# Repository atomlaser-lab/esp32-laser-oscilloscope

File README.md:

# ESP32 Remote Oscilloscope + MOGLabs DLC control

This project is a remote browser-based oscilloscope and controller intended for monitoring, toggling and adjusting the frequency lock on a MOGLabs Diode Laser Controller (DLC). An ESP32 development board interfaces with the DLC and hosts a dashboard webpage.

This README contains [Instructions](#instructions) for setting up and using the project as well as useful [Background information](#background). A list of [bugs and suggested improvements](#bugs-and-improvements) is at the end. The project was developed and tested using the PlatformIO Extension in VSCode, with a model 502 DLC. It requires an ESP32-DevkitC development board (see [specs, board comparison & resources](https://www.espressif.com/en/products/devkits/esp32-devkitc)), and should work with either WROVER or WROOM versions. It was tested with the ESP32-DevKitCVE V4 board, which has a WROVER module.

## License
[GPLv3](LICENSE)

## Repository structure
Branches: currently just `esp`. Branches for other microcontrollers might be useful in future.

PlatformIO:
- `src/main.cpp`: ESP32 code.
- `data/`: files stored on the ESP32 flash memory. Contains the webpage + `config.json`.
- `platformio.ini`: PlatformIO project config.

Hardware:
- `board-design/`: TODO
- `enclosure/`: FreeCAD files for the 3D-printable housing.

Other:
- `.vscode`: recommended extensions
- `assets/`: images for this README.

## Instructions
[Software config](#program-configuration-and-upload) - [Hardware](#hardware-connections-and-settings) - [Browser interface](#interface)

### Program configuration and upload
This section assumes you are using the PlatformIO extension in VSCode.

Specify project options by editing `config.json` (in `/data`). If connecting to an existing WiFi network (the default option), you must specify its `ssid` (network name) and `password`. If instead `host` is set to `true`, the ESP will host its own network (intended for testing purposes) with credentials `host_ssid` and `host_password`. `host_password` must contain at least 8 characters; otherwise hosting will fail. Note that the ESP32 only supports 2.4GHz WiFi (not 5G).

Other parameters are optional, with defaults and descriptions as shown below in **Example 2**.

**Example 1: minimal WiFi connection**
```
{
  "ssid": "MyWiFiNetwork",
  "password": "verysecurepassword",
}
```

**Example 2: all options**
```
{
  "name": "TestName",
  "host": false,
  "ssid": "MyWiFiNetwork",
  "password": "verysecurepassword",
  "host_ssid": "ESP32_Laser_Lock",
  "host_password": "laserlock",
  "host_channel": 1,
  "default_duration": 60,
  "default_resolution": 2,
  "default_ip": "192.168.1.1"
}
```

| Parameter | Description |
| --- | --- |
| `name` | Display name for the device |
| `host_channel` | If hosting, the WiFi channel used. |
| `default_duration` | Default length of a measurement packet (millisec), adopted on board startup. |
| `default_resolution` | Default time (ms) between consecutive samples in a measurement packet, adopted on startup. |
| `default_ip` | If available, the local IP address the ESP32 will adopt. Applies to both hosted and external networks. |

To **upload the project to the board**:
1. Connect the board to your computer via a cable.
2. Upload the filesystem to the board:
    - '*Build filesystem Image*' (in PlatformIO menu)
    - **Ensure all serial monitor connections with the board are closed**. PlatformIO does not do this automatically when uploading the filesystem (though it *does* when uploading the code in step 4)
    - '*Upload filesystem Image*' (in same menu)
3. '*Build*' (PlatformIO menu, or tick symbol in status bar)
4. '*Upload*' (PlatformIO menu, or rightwards arrow in status bar)

The program will restart each time the ESP is plugged in, code/filesystem is re-uploaded, or the RST button is pressed.

Open the serial monitor to see the board's local IP. You may need to reset the program (RST button) while the monitor is open for the message to display. If `default_ip` is specified (and was successfully adopted), you can skip this step.

Connecting to the board's IP in a browser (e.g. `http://192.168.1.1`) while on the same network will open the [Interface](#interface).

### Hardware
This section assumes you already have a laser-locking setup using the MOGLabs DLC. For information about laser locking and the DLC, see [Background](#background).

#### Overview
The MOGLabs DLC contains fast, robust analog control circuitry for locking the laser frequency. The point of this project is to allow the lock to be acquired via microcontroller control of the DLC, while leaving the DLC to handle the actual locking process.

The project currently has three inputs and three outputs. The photodiode , error and trigger (digital) signals from the DLC are input to the board and transmitted to the remote user interface. The board outputs two digital (TTL) control signals to enable/disable the FAST and SLOW lock, and an analogue signal (via external DAC) to adjust the laser's frequency offset. More detailed reasoning behind the electronic design is explained in [Hardware design](#hardware-design).

The next section contains some guidance for putting together the PCB. The ESP32 board can be soldered to the PCB directly for the smallest possible footprint, but it is much more flexible to attach it via additional male and female headers. The external frequency offset voltages used in this project also require soldering an additional resistor into the DLC (see [Connecting to the Diode Laser Controller](#connecting-to-the-diode-laser-controller)). 

Part numbers and quantities for **two** PCBs are specified in `board-design/moglabs-remote-locking-board.txt` for the DigiKey electronics distributor, which can be imported directly into a DigiKey cart. This list is missing capacitors C6 and C7 (see table below). Auxiliary parts (headers + DLC resistor) are similarly specified in `board-design/auxiliary-parts.txt`. An optional 3D-printable housing for the project can be found under `enclosure/`. 

Electronic design was done in KiCAD 6, and the (optional) enclosure was generated with FreeCAD 0.20.2.

#### Printed Circuit Board
Relevant files are in `/board-design`. Gerber files for manufacturing the PCB can be found in `generated.zip`, and PCB circuit and layout schematics (`.pdf`) are under `plots/`.

```
board-design/
|-- generated.zip
|-- plots/
  |-- moglabs-remote-locking-board.pdf
  |-- moglabs-remote-locking-board.pcb
|-- moglabs-remote-locking-board.txt
|-- auxiliary-parts.txt
|-- ...
```

This section briefly describes the circuit, shown below. For more details, see `board-design/README.md`.

Left: input for the error signal ('Lock'), photodiode signal ('PD') and trigger. A 1.5V offset is added to the (bipolar) error signal to make it positive, and both Lock and PD voltages are clipped to remain within the board's 0-3.3V pin range. The DLC trigger is +5V, which is divided down accordingly.

Bottom left: power regulator to introduce +5V and -5V VDD and VSS rails from the board's 5V power pin.

Right: analog frequency-offset output signal (J6) controlled by an external DAC (U4) and dual opamp (U3). The DAC output is divided down considerably, as a 1V adjustment to PZT MOD corresponds with about a third of the piezo's (i.e. frequency) range. A variable resistor gives additional control over the output voltage range (this will need to be tuned to observe an output signal).

The required parts for **one** PCB are in the tabe below. For specific part numbers, see the DigiKey text files specified above. Note that the capacitor numbering in the schamatic skips C8.

Terminology:
- 8-SOIC is a component shell size/type (comonly opamps, dacs)
- DAC: digital-to-analogue converter
- SPI: Serial Peripheral Interface
- SMD: Surface-mounted device
- 1206: component size

| Requirement / Part description | PCB Locations | Total Qty | Notes |
| --- | --- | --- | --- |
| IC 8SOIC 12-Bit single-output DAC with SPI and internal voltage reference (2.048V/4.096V) | U4 | 1 | code assumes [MCP4821](https://www.microchip.com/en-us/product/MCP4821) |
| IC 8SOIC JFET opamp 1-circuit | U1 | 1 | |
| IC dual (2-circuit) opamp GP 8SOIC | U3 | 1 | |
| ESP32 DevKitC VE (WROVER/WROOM) | U2 | 1 | |
| 16-position 2.54mm female row header | J5, J9 | 2 | |
| 2-pos 2.54mm male header | J1 | 1 | |
| 50 kΩ potentiometer 0.5W | RV1 | 1 | |
| DC DC converter dual 5V 1W | PS1 | 1 | |
| BNC socket | J2, J3, J4, J6 | 4 | |
| 40V 1A Schottky diode (SMD 1206) | D1,D2,D3,D4,D5 | 5 | |
| 100 nanofarad 50V ceramic capacitor (SMD 1206) | C3, C4, C5, C9, C10 | 5 | |
| Polarised through-hole capacitor 4.7 uF 25V | C1, C2 | 2 | |
| 10 nF through-hole capacitor | C6 | 1 | Not on DigiKey list |
| 100 nF through-hole capacitor | C7 | 1 | Not on DigiKey list |
| 10 kΩ 0.5W resistor (SMD 1206) | R2, R3, R4, R7, R9 | 5 | |
| 20 kΩ 0.5W resistor (SMD 1206) | R10 | 1 | |
| 100 kΩ 0.5W resistor (SMD 1206) | R6, R12 | 2 | |
| 3.9 kΩ 0.25W (SMD 1206) | R14 | 1 | |
| 56 kΩ 0.25W resistor (SMD 1206) | R1 | 1 | |

Optional headers for mounting the ESP32 devkit on the PCB:

| Description | PCB Locations | Total Qty | Notes |
| --- | --- | --- | --- |
| 19-position 2.54mm female header | J7 & J8 (not marked) | 2 |  |
| 19-position male header for ESP32 | On ESP32 | 2 | Likely included with ESP32 devkit |

#### Tests
- TODO

#### Connecting to the Diode laser controller
Take care when connecting to the DLC, particularly to avoid shorting the digital control pins. Ensure the internal DIP switch settings of the DLC are set appropriately (e.g. as in [Moglabs Diode Laser Controller](#moglabs-diode-laser-controller)). For reference, at the end of this section are the DLC panels (from the [DLC manual](https://www.moglabs.com/products/laser-electronics/diode-laser-controller)) and the location of the HD12 header.

##### **POWER**
The board can be powered via the micro-USB connector (5-12V) or the PCB's J1 two-pin header (5V).

The DLC has an IEC output (rear panel, second from the left), which is a direct connection to the DLC's input power (after the mains filter) and can be used to power the ESP32 using an IEC cable and 12V power adapter. This is convenient and ensures the ESP32 shares the same ground as the DLC.

Safe input voltages for the board's pins are 0-3.3V, and is it **not** tolerant of voltages outside this range. Be careful to keep the DLC and ESP32 ground voltages compatible.

##### **SLOW and FAST**
Digital control of the DLC is via the internal HD12 header, which is located as shown below. **Do not** confuse it with the similar-looking header nearby. The ESP's digital pin voltages are compatible with the HD12 header and can be connected directly as per the table below.

| Board pin | HD12 pin(s) |
| --- | --- |
| GPIO14 | 3 |
| GPIO4 | 5 |
| GND | 4, 6 |

Ensure that the sweep range is set appropriately, and that the front-panel LOCK and FAST switches are **off** so that these can be enabled remotely.

##### **TRIGGER**
The MOGLabs DLC trigger signal output (TRIG on rear panel) fires a +5V rising edge (i.e. 0V to 5V) at the trigger point of the sweep, i.e. the *centre* if using the DLC's default (internal) sweep. This can be safely connected to the appropriate BNC input on the PCB.

##### **INPUT SIGNALS**
Set the CHAN A and CHAN B selector dials to (photodiode) Input and (feedback) Error respectively; note that both channels can output the photodiode, but only CHANNEL B can output the error signal. Connect these to their respective PCB inputs.

The photodiode input offset and error signal offset can be adjusted respectively using the INPUT and ERROR OFFSET dials on the DLC's front panel. The photodiode should be in the range 0-3.3V, and the error centred for locking (i.e. about zero).

##### **FREQUENCY CONTROL**
Test the frequency control output (J6) before connecting, to ensure it is within the range +/- 0.2V. Before connecting, a 5kΩ resistor must be added at location R113 on the DLC's circuit board to allow adding an external frequency voltage offset.

| Description | **DLC** location | Total Qty |
| --- | --- | --- | --- |
| 5kΩ size 0603 SMD resistor  | R113 | 1 |

Once this is added, connect J6 via BNC to the DLC's SWEEP/PZT MOD input.

##### Reference images

**Location of HD12 Header**

**Front DLC panel**

**Rear DLC panel**

### Interface
Connecting to the board's IP in a browser should display the page below. If you didn't set the IP in `config.json`, you can list the devices on the local network using `arp -a` in a terminal, or check the IP by restarting the ESP32 while connected to the serial monitor.

Only one user is allowed to connect at a time, to prevent conflicting commands.

Controls for the DLC, the ESP32, and the browser display are split into three separate panels.

#### DLC Control
The top panel has switches for toggling the SLOW and FAST lock. These switches are subject to a cooldown, and will also only change appearance once the ESP has confirmed the command was successful.

The 'Frequency Offset' slider controls the external voltage to the piezo. The displayed number is arbitrary.

#### Sampling settings
Signal measurements are sent from the board to the browser in groups. The RESOLUTION and DURATION sliders respectively control the time between individual measurements and the size of each group sent to the browser.

#### Display settings
These affect how the signal is displayed in the browser. Check 'Remember' to remember these settings.

| Slider| Function |
| --- | --- |
| DIV | Time period represented by each horizontal interval on the display. (i.e. horizontal scaling) |
| POSITION | Horizontal position of the trigger point in the signal, marked by the yellow indicator. |
| PERSISTENCE | How quickly previous trigger signals fade from the screen. |
| LINE | The line thickness. |

## Background
This section explains useful background on laser operation and the MOGLabs DLC, as well as summarising relevant details about the ESP32 and giving an overview of how the program works.

### Lasers (motivation and operation)
In various applications we would like to 'lock' the frequency of a laser to a specific atomic transition frequency, either because these are physically constant and known to high precision or because we are working with that particular transition.

The output power and frequency of an external-cavity diode laser (ECDL) (TODO: useful reference here) are controlled primarily (though to differing extents) by three factors:

1. Current injected to the diode
2. Temperature
3. Cavity length (controlled by piezo voltage).

An ECDL internally permits light to (co)exist at a discrete set of frequencies ('modes') determined by the length of the cavity. This light bounces back and forth through a 'gain medium', which repeatedly amplifies it (up to the limit of power provided by the injection current). On each trip, a small amount exits the cavity. The diagram below is an example of frequency-dependent gain (black) affecting different modes (red) (image credit: [this stackexchange answer](https://physics.stackexchange.com/questions/355223/laser-gain-curve) under the [CC BY-SA 4.0 license](https://creativecommons.org/licenses/by-sa/4.0/)).

At a given temperature and injection current, the gain medium amplifies different frequencies by different amounts, known as a gain curve. When 'lasing' (i.e. sufficiently high current), the most strongly-amplified of the allowed modes will quickly dominate, producing a single-frequency output (provided this amplification is enough to overcome losses).

Even with constant current, temperature and cavity length, the laser frequency tends to drift, which is mitigated using feedback. However, if two modes have similar amplification, the dominant one can switch erratically ('mode hopping') with a corresponding distinct jump in frequency. These jumps typically can't be remedied by feedback, requiring the laser to be re-locked. The aim of this project is to allow this re-locking to be performed remotely.

### Frequency locking (Saturated absorption spectroscopy)
To produce an error signal, we make use of the fact that an atom will only absorb light that is near a transition, roughly within a linewidth (i.e. ~inversely proportional to the lifetime of the corresponding state). Linewidths vary between kHz and GHz.

[ TODO: diagram of vapour cell with counterpropagating beams ]

Suppose a laser passes through a gas. The *apparent* frequency of the laser depends on the velocity of an atom (the Doppler effect). Since the atoms have a range of velocities, the laser will be absorbed in rough proportion to the number of atoms at the corresponding velocity, so the range of absorbed frequencies is 'Doppler-broadened' and the output intensity varies on the order of GHz.

If we reflect the laser back through the cell, it will now excite (i.e. be absorbed by) atoms of the *opposite* velocity, reducing the intensity again. This will not occur, however, if these atoms were *already* excited by the forward beam, i.e. if the beam is exactly on resonance with the zero-velocty atoms. So, we get a small dip in absorption when at the transition frequency.

[ TODO: diagram of doppler-broadened peak and saturation dip]

[ TODO: diagram of Rb85 absorption spectrum and error signal, e.g. DLC manual Fig. 1.3]

We can use the absorption dip as a reference point via either *AC* or *DC* locking. In both cases, we first produce an *error signal* whose voltage indicates the sign and size of any frequency drift, being zero at the reference point. Any error is then corrected via a feedback signal to the laser.

DC locking uses the absorption signal itself (as measured by the photodiode) as the error signal, by applying a voltage offset so that the signal passes zero on the side of the absorption peak. However, this easily becomes unlocked as the laser power drifts relative to the reference voltage.

AC is more reliable and allows you to lock exactly to the peak of a signal. This is done by rapidly shifting the signal from side to side, by deliberately modulating (dithering, i.e. rapidly oscillating) either the laser frequency (via the injection current) or the atomic resonance frequency (via a magnetic field). The MOGLabs DLC supports both methods, but in this case we used the former. Passing the modulated signal through a lock-in amplifier yields the derivative of the absorption spectrum, which passes through zero at the centre of the peak and hence serves as an error signal.

### MOGLabs Diode Laser Controller
This section is a reference for how the DLC works, convering information relevant to the design and understanding of the project. It summarises parts of the MOGLabs DLC manual (description and manual [here](https://www.moglabs.com/products/laser-electronics/diode-laser-controller)) and my own experience. The DLC's settings are mostly controlled via internal DIP switches (small, manual switches). Below is a reference; selections used in this project are in bold, and a brief explanation is on the right. The rest of this section will hopefully make clear what these DIPs do. 

| DIP Switch | Off | On | Relevance |
| --- | --- | --- | --- |
|1 | **DISC fixed** | DISC ON| Our laser doesn't have DISC |
|2 |STACK fixed| **STACK ON**| Enables control of the piezo |
|3 |Current dither OFF| **Current dither ON** | Enables *laser current* modulation when OFF/MOD is enabled |
|4 |Current bias OFF| **Current bias ON**| Enables BIAS, to avoid mode hopping|
|5 |**Internal error**| External error| We use the DLC's generated error signal
|6 |**External current mod OFF**| External current mod ON| Leave the DLC to do its thing
|7 |**AC lock**| DC lock| AC locking is more reliable
|8 |**Single photodiode**| Dual photodiode| Measuring direct intensity or the difference of two intensities, using the MOGLabs photodiode.
|9 |**Sweep internal**| Sweep external| Internal sweep works well, and SWEEP/PZT mod is needed for electronically adjusting the frequency offset
|10| STACK feedback –| STACK feedback +| Depends on your setup
|11| STACK sweep +| STACK sweep –| Depends on your setup
|12| **AC current feedback** | DC current feedback| FAST feedback should usually be AC no matter what
|13| **STACK internal**| STACK external| We want the DLC to control STACK, not us.
|14| DISC internal| DISC external| Irrelevant if no DISC.
|15| Default| External slow error| See manual
| 16 | See manual.

The DLC controls all three of the ECDL's piezo voltage (cavity length), temperature and injection current. The voltage applied to the piezo is known as the STACK (some lasers have a second piezo, *DISC*, which can also be controlled - I ignore that here.). At any given time, the DLC is either SCANning or LOCKing the laser frequency.

The voltage supplied to STACK ranges from 0-120V. When scanning, this voltage is adjusted according to the DLC's *sweep signal*, which has a range of 0-2.5V. The width of the scan (corresponding with full 0-2.5V range) is controlled by the SPAN dial and cannot be controlled externally. The DLC's trigger fires when the sweep signal crosses 1.25V; when locking is activated, the laser is first moved to this point before locking to the nearest zero-crossing of the error signal. Offsets to the input signal and error signal are adjusted using the INPUT OFFSET and ERROR OFFSET dials, respectively.

The DLC can either generate its own internal sweep signal, or use an *external* signal input to SWEEP/PZT MOD. The direction (polarity) of the internal sweep can be chosen using DIP switch 11, and its frequency can be varied between 4Hz-70Hz using the *fsweep* front panel trimpot. Diagrams of the internal sweep and corresponding trigger output are provided in the manual (Fig. 1.2). The sweep sawtooth is illustrative only; the DLC doesn't produce a sawtooth with perfectly vertical edges - they actually have a slight slope, to prevent the piezo from snapping back into place too forcefully (which creates a rattling sound). If this still happens, you may need to reduce the sweep frequency (fsweep trimpot) or SPAN.

The piezo offset (i.e. laser frequency) at the lock point is determined by the FREQUENCY dial. In particular, it is *not* affected by the use of an external sweep signal, which is only useful for controlling the speed, shape and (potentially asymmetric) width of the frequency path up to the maximum width set by SPAN. To limit mode-hopping while scanning, the diode current can be 'biased' to adjust itself linearly with the sweep voltage; this is enabled using DIP switch 4, with the direction and extent of adjustment controlled by the BIAS front trimpot.

#### Locking
The DLC provides feedback to the laser via:

1. The (relatively SLOW) piezo - for larger, slower drifts
2. The (comparably FAST) injection current - for small, rapid frequency fluctuations.

Each feedback is enabled by the corresponding switch (or digital control), and the direction can be reversed using DIP switch 10. The choice of AC or DC locking is controlled by DIP 7. The DLC provides an optional 250kHz modulation (switch OFF/MOD on front panel), either as an output (for e.g. dithering the atomic resonance) or directly to the laser current (see DIP switches); this is intended to aid AC locking. In either case, the amplification of the error, slow feedback and fast feedback can each be adjusted from 0-40dB via the GAIN, SLOW and FAST dials respectively. In the AC case, the phase of the lock-in amplifier (PHASE) may also need adjusting. Phase can be used to switch the sign of the SLOW feedback; to switch the sign of the FAST feedback, use the +/- switch. Note that the the MOGLabs photodetector outputs 30mV/microWatt.

Depending on which DIP switches are active, the SWEEP/PZT MOD input (rear panel) allows replacement of either the sweep signal (DIP 9), error signal (DIP 15) or direct piezo control voltage ('STACK') (DIP 13) with an external signal. However, the **only option** to externally adjust the lock frequency while making use of the DLC's (fast, robust, analogue) inbuilt control circuitry is to instead add a resistor (~5kΩ, size 0603) at location R113 (see the DLC manual), while leaving the aforementioned DIP switches OFF. This *adds* the SWEEP/PZT MOD input voltage to the existing laser piezo signal (STACK) under all circumstances (after a 48x scaleup).

Digital control of the DLC is via its internal HD12 control header, with the following pins:

| Pin | Signal |
| --- | --- |
|1 | Laser ON (low: off) |
|3 | Slow Lock (low: sweep) |
| 5 | Fast Lock |
| 7 | Hold |
| 9 | +5V |

Pins 2,4,6,8,10 are ground. 

These control pins are OR-ed with the front panel switches, so digital locking control only applies if the SCAN/LOCK switch is set to SCAN, and (for fast lock) the OFF/LOCK switch to OFF.

### ESP32
The ESP32 is a system-on-chip (SoC) with built-in WiFi, with input-output access via a *module*. For ease of use, this is often mounted on a *development board*, which provides easy pin access and various other useful components (e.g. ADC, voltage regulation). The same board 'form factor' (shape and pin arrangement) can be paired with different module versions; this project requires a ESP32-DevKitCVE V4 board, either with the ESP32-WROOM or ESP32-WROVER module.

An excellent introduction to the ESP32 can be found at [Last Minute Engineers (LME)](https://lastminuteengineers.com/getting-started-with-esp32/). This includes tutorials on ESP web servers and GPIO interrupts, both of which are used in this project. However, their tutorial uses (1) an older and slightly different board and (2) the Arduino IDE, while this project was developed using the PlatformIO IDE for VSCode (including the instructions in this README). 

An excellent video tutorial for PlatformIO+VSCode can be found [here](https://www.youtube.com/watch?v=JmvMvIphMnY). The project's source code uses the ESP32 Arduino framework ([documentation here](https://espressif-docs.readthedocs-hosted.com/projects/arduino-esp32/en/latest/index.html)). 

For the DevKitC-V4, a look at the [Getting Started Guide](https://docs.espressif.com/projects/esp-idf/en/v4.4.5/esp32/hw-reference/esp32/get-started-devkitc.html). Detailed specs can be found in the [official ESP32 datasheet](https://www.espressif.com/sites/default/files/documentation/esp32_datasheet_en.pdf). Below is the pin reference from the Getting Started Guide (note GPIO stands for General Purpose Input Output):

Note that not all pins are safe to use; this is discussed more in [Hardware design](#hardware-design).

The ESP32 has two 12-bit analog-to-digital converters (ADCs), which together can read analogue inputs from fifteen pins; however, ADC2 cannot be used while WiFi is in use, and so the analog input pins for this project have been chosen from those available to ADC1. Note that this issue prevents use of the (similar but less powerful) ESP8266 for this project, as it has only one ADC (which is WiFi-blocked).

ESP32 also has [a digital-to-analog converter](https://docs.espressif.com/projects/esp-idf/en/latest/esp32/api-reference/peripherals/dac.html) (DAC); however, this was not sufficient for this project.

The ESP32 only operates on 2.4GHz WiFi band (not 5.8GHz). The longevity commitment for the original ESP32 module is until [Jan 1, 2028](https://www.espressif.com/en/products/longevity-commitment)

### Hardware design
This section explains some details affecting the electronic design of the PCB.

The pins on the ESP32-DevKitC-V4 are (officially) only tolerant of 0-3.3V voltages, requiring appropriate input clipping for protection. The DLC's trigger is a 0-5V square signal, 

The previous section noted that only one of the ESP32's two ADCs can be used concurrently with WiFi. More importantly, WiFi use causes periodic spikes in power draw, which adds enough noise to the DAC output to prevent successful laser locking. Neither the board's inbuilt power regulator, nor additional bypass capacitors on the frequency-control output signal, are enough to avoid the issue. Therefore, we use an external MCP4821 DAC controlled via Serial Peripheral Interface (SPI). This also has a 12-bit resolution, higher than the inbuilt 8-bit DAC. The impedance of the SWEEP/PZT MOD input on the DLC is 5kΩ.

#### Pin choice
Can't use TX & RX pins, as they're used when flashing the board (even via USB). Pins which affect boot mode (0, 2, 12, 15) have been left alone. WROVER reserves GPIO 16/17 for internal use (controlling the SPI PSRAM). Inbuilt DAC (GPIO25/26) and the remaining ADC1 pins (GPIO33,32,35) have also been left available.

See Last Minute Engineers and [the boot mode docs](https://docs.espressif.com/projects/esptool/en/latest/esp32/advanced-topics/boot-mode-selection.html).

#### External DAC

This project uses the MCP4821 DAC to produce the frequency-adjustment signal, controlled from the ESP32 via serial peripheral interface (SPI).

The ESP32 has two SPI buses available for general use: SPI2 (HSPI) and SPI3 (VSPI). 'H' and 'V' don't signify anything. Any pins can be set as the corresponding interface pins; the defaults are indicated in the pinout diagram, but in this project non-default pins are used.

SPI communication with the MCP4821 is explained in its datasheet. Briefly: chip-select is driven LOW to initiate each data transfer, then 16 bits are transferred: four config bits followed by 12 value bits. The value bits are stored in the DAC's input register, and transferred to the output (Vout) when LDACn is pulled low. The current software keeps LDACn permanently low, so that the input value is transferred immediately to output.

### Software design
This section gives a general overview as well as some relevant details of the code. Many more comments are scattered throughout the source.

On startup, the ESP32 reads from `config.json`, sets up WiFi as a host or station accordingly, and begins a webserver (run asynchronously in the background) to serve the static webpage interface. Only one user is allowed to connect at a time, to prevent conflicting commands.

Since the MOGLabs DLC fires its trigger in the *middle* of each sweep, the simplest way to capture the entire sweep is to continually measure the input signals. The signal is sampled in 'packets', with a certain interval between each sample (~0.1-10ms), and a specified packet duration (~30ms-1s) before it is sent to the web client and a new packet begun. For simplicity, each 12-bit ADC measurement is reduced to a single byte (8-bit). Triggers fire an interrupt which records the time of the trigger in microseconds. When a packet is complete, a 'herald' message (JSON text) is sent over the websocket, containing the packet's start and end time (microseconds) as well as the trigger time (if any). The measurements themselves are then sent on the websocket as a binary buffer (note that websocket messages are always reconstructd in-order by the client).

On the web client, received packets are stored and displayed according to the most recent trigger, with packets from previous triggers faded (but still visible). This was originally designed to allow gaps between measurement packets to be filled by previous packets, though there is no longer a significant gap. Old data is culled from time to time.

Messages sent from client to the board to control the laser frequency offset are sent as two-byte integers over the websocket. Commands for toggling the lock and updating the measurement interval/duration are sent via HTTP. The interface waits until it receives confirmation of success from the ESP before updating the SLOW/FAST switches. Messages are sent periodically (every 10s) to check the control-state of the DLC; this is also done when toggling the lock.

`cpp` source code: in the Arduino framework, the pin number is the GPIO number (at least in PlatformIO).

## Bugs and improvements

### Known bugs
- (Serial monitor) `ERROR: Too many messages queued`. The ESP32 has a message queue limit of 16 and any others will just be discarded. When the sampling duration is small it is unable to flush the queue frequently enough.
- (Serial monitor) `open(): /littlefs/file does not exist`
  - this is a meaningless error, and to get rid of it you have to modify `ESPAsyncWebServer/src/WebHandlers.cpp` 
  - See https://github.com/lorol/LITTLEFS/issues/2

### TODO
- Save HD12 & DAC settings on reset
  - Allow config file to be modified remotely?
- DLC-safe reset procedure
- Look into uploading the config file Over-The-Air.
- Vertical DIV scaling on display, independently for photodiode and error signals.
- "Invert signal" button
- Reset sample-settings sliders to their previous value if HTTP POST message fails.

### Suggested improvements
- Mobile-friendly webpage (cf. `@media-query`)
- Optional user authentication
- Automatic mode-hop detection and re-locking
- Higher monitoring resolution? (Currently 8-bit, but ESP32 ADCs are 12-bit)
- Input modes: continuous, on-request, single trigger
- Highlight clipped sections of the signal in red
- Button to remotely restart the ESP32 and/or restore default measurement settings.
- Cookies for display settings don't seem to be respected when the board restarts.
- Interface information
  - Warnings/errors from the ESP
  - Websocket connection status
  - Actual measurement resolution of most recent packet
- README
  - Serial monitor error message reference for custom errors

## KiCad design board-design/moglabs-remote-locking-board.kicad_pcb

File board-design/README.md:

# Circuit and PCB for remote locking

This PCB and associated enclosure is intended to be used in conjunction with an ESP32 development board for the purposes of providing a remote interface for locking MOGLabs diode lasers.  It is intended that the MOGLabs DLC handles the locking process, and that this board and its circuitry is used for acquiring the lock.  The PCB provides a convenient way of acquiring input signals and producing an appropriate output signal for the DLC.

PDFs of the circuit diagram and the PCB can be found under the plots/ directory.  Electronic design was done in KiCAD 6, and the enclosure was generated with FreeCAD 0.20.2.  Gerber files for manufacturing the PCB can be found in "generated.zip".  Digikey part numbers and quantities for 2 boards can be found under 'moglabs-remote-locking-board.txt' and 'auxliliary-parts.txt'.

## Circuit design

The idea behind this project is to use a WiFi-enabled microcontroller to measure locking signals from a diode laser, present those to a user through a web interface, accept user input to enable the lock or change the lock position, and then to produce output signals to act on user input.  The core of the board is an ESP32-DevKitC-v4 board, which can use a number of different microcontrollers but with the same board pinout and form factor.  The part chosen for this project is the ESP32-DEVKITC-VE with an ESP32-WROVER-E microcontroller.  Other chips with the same pinout and form factor can also be used.

Two analog signals are recorded by the microcontroller unit (MCU): the error or locking signal, denoted as "Lock", and the raw photodiode signal, denote as "PD".  The MCU's ADCs can only record positive voltages, and the error signal by definition must be bipolar, so an op-amp and associated components is used to add a 1.5 V offset to the signal while also inverting it (the inversion is simply a side-effect).  This should put the error signal at the midpoint of the ADC's voltage range.  A pair of Schottky diodes is used to clip the voltage to the 0 V and 3.3 V rails.  The PD signal should always be positive, and it is similarly clipped to the 0 V and 3.3 V rails.  The Lock signal is recorded using ADC1_CH0 or GPIO36, and the PD signal is recorded using ADC1_CH3 or GPIO39.  Finally, the trigger generated by the MOGLabs DLC is recorded using the digital input channel GPIO34 after passing through a voltage divider to bring the 5 V level to 3.3 V.  As the actual lock is handled by the DLC the quality of the recorded input signals is not particularly important, and we have thus used the MCU's internal ADCs.

The output analog signal is more important, and the on-board DACs don't work well when the WiFi is also running.  Therefore, we use a 12-bit DAC (MCP4821) which interfaces with the MCU via SPI to produce the output signal for the external piezo control.  The DAC produces a unipolar output, so one channel of a dual-channel op-amp is used to offset the voltage and generate a bipolar output.  The DAC in this case has a selectable voltage reference, and here we have assumed that it is set such that the reference voltage is 4.096 V which is also the default on power-on.  Resistors R6, R7, R12, and R14 are chosen to produce voltage outputs as close as possible to a bipolar output.  The resistors are chosen to give an approximate +/-0.2 V output range.  The second op-amp is combined with a trimmer potentiometer to give more control over the output voltage range.  Both amplifiers operate in an inverting configuration, which gives a net non-inverting output.

It is expected that power will typically be supplied via the development board's USB connector, which is nominally +5 V.  However, users can instead supply +5 V to the J1 pin header, which will power both the development board and the rest of the circuitry.  Bipolar +/-5 V is generated by the switched-mode power supply PS1, and the VDD and VSS pins on the op-amps are connected to the appropriate pins on the power supply.  This power supply can supply up to 100 mA, and it technically has a minimum load of 10 mA, but the datasheet states that no damage will occur if operated with loads below 10 mA.  It is expected that output ripple will probably be worse than specified if the current draw is less than 10 mA.  If a bipolar supply is present, one could not populate PS1 and instead connect the bipolar +/-5 V rails to the appropriately labelled connections on the board, possible through the use of a standard 2.54 mm pitch pin header.  Users would then need to connect the +5 V rail to the development board.

The development board can be connected to the PCB in one of two ways.  The first is to solder male pin headers to the PCB and then solder the development board to the male pin header: this will provide the smallest possible footprint.  The second way is to solder female pin sockets to the PCB and then solder male pin headers to the development board and attach it to the PCB in a solder-less connection.  This is probably the better option, even though it involves more soldering, because if the development board needs to be removed it is a hassle to de-solder 38 separate pins.

Finally, most of the GPIO pins on the development board are broken out on the female pin sockets J5 and J9.  When programming, the user can choose appropriate GPIO pins for driving the DLC digital control pins.  It is recommended that wires connected to male pin headers are used for the connection.

The PCB has four M3 mounting holes in the corner of the board.  These can be safely used with standard metal bolts as they are not connected to any of the electrical signals.

## Enclosure

The enclosure is designed with the expectation that it will be 3D printed.  The interior of the box has four posts intended for attaching the PCB via the M3 mounting holes.

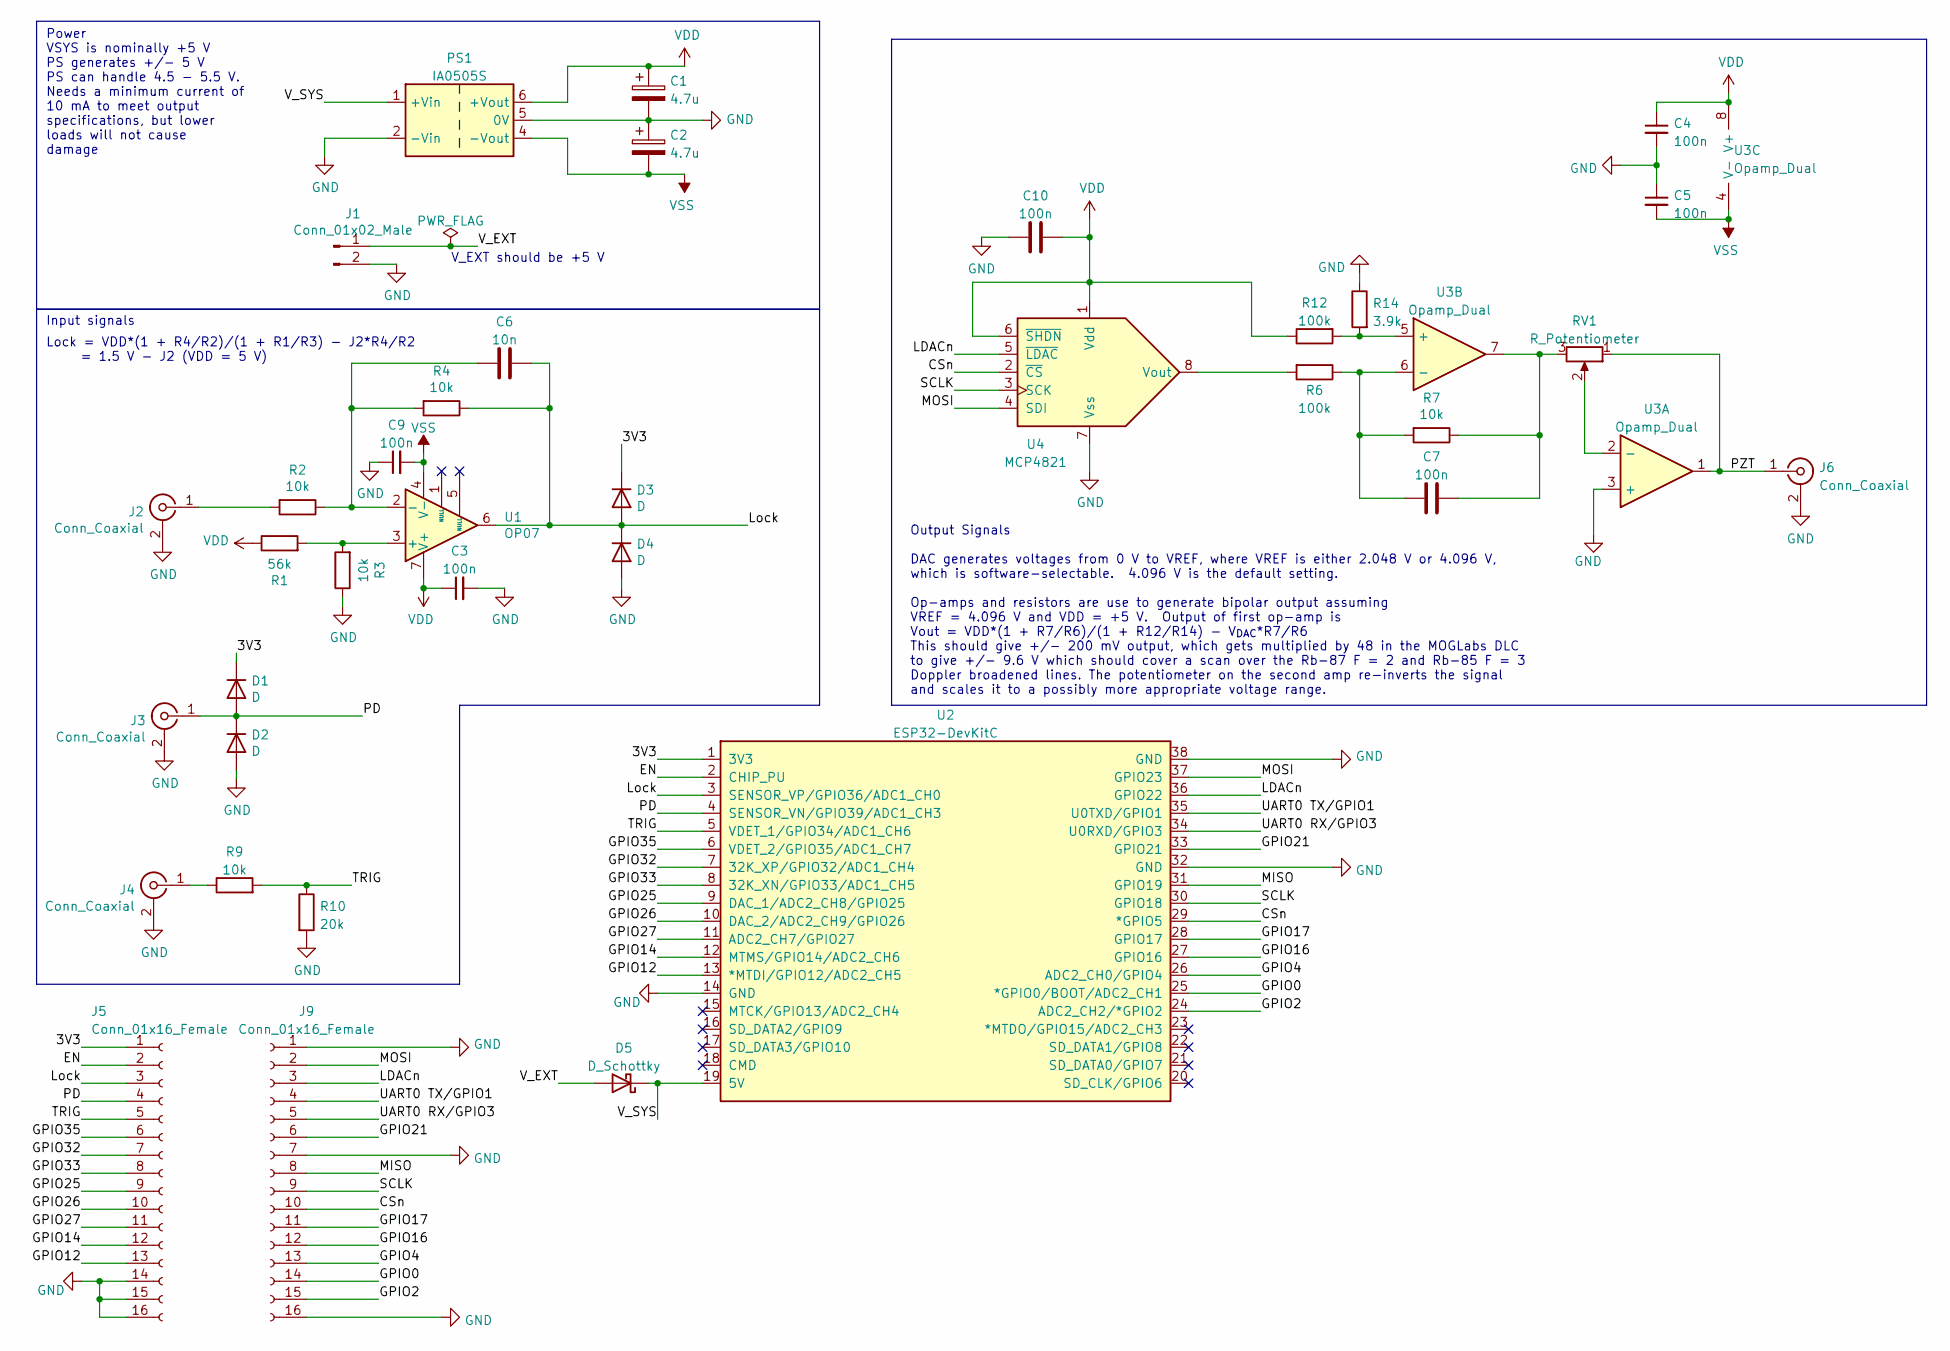
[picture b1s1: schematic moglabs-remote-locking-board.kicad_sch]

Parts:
C1, C2: 4.7u; CP_Radial_D5.0mm_P2.00mm; Digikey Part Number 732-8935-1-ND
C3, C4, C5, C9: 100n; C_1206_3216Metric_Pad1.33x1.80mm_HandSolder; Digikey Part Number 399-C1206C104K5RAC7210CT-ND
C6: 10n; C_Disc_D5.0mm_W2.5mm_P2.50mm
C7: 100n; C_Disc_D5.0mm_W2.5mm_P2.50mm
C10: 100n; C_1206_3216Metric_Pad1.33x1.80mm_HandSolder
D1, D2, D3, D4: D; D_1206_3216Metric_Pad1.42x1.75mm_HandSolder; Digikey Part Number 478-7809-1-ND
D5: D_Schottky; D_1206_3216Metric_Pad1.42x1.75mm_HandSolder; Digikey Part Number 478-7809-1-ND
J1: Conn_01x02_Male; PinHeader_1x02_P2.54mm_Vertical; Digikey Part Number 2057-PH1-02-UA-ND
J2, J3, J4, J6: Conn_Coaxial; BNC_Molex_0731000167; Digikey Part Number WM4089-ND
J5, J9: Conn_01x16_Female; PinSocket_1x16_P2.54mm_Vertical; Digikey Part Number 61301611821-ND
PS1: IA0505S; Converter_DCDC_XP_POWER-IAxxxxS_THT; Digikey Part Number 1470-IAB0105D05-ND
R1: 56k; R_1206_3216Metric_Pad1.30x1.75mm_HandSolder; Digikey Part Number RMCF1206JT56K0CT-ND
R2, R3, R4, R7, R9: 10k; R_1206_3216Metric_Pad1.30x1.75mm_HandSolder; Digikey Part Number RNCP1206FTD10K0CT-ND
R6, R12: 100k; R_1206_3216Metric_Pad1.30x1.75mm_HandSolder; Digikey Part Number 738-RNCP1206FTD100KCT-ND
R10: 20k; R_1206_3216Metric_Pad1.30x1.75mm_HandSolder; Digikey Part Number RNCP1206FTD20K0CT-ND
R14: 3.9k; R_1206_3216Metric_Pad1.30x1.75mm_HandSolder; Digikey Part Number RMCF1206FT3K90CT-ND
RV1: R_Potentiometer; Potentiometer_Bourns_3266W_Vertical; Digikey Part Number 987-1508-ND
U1: OP07; SOIC-8_5.23x5.23mm_P1.27mm; Digikey Part Number 296-TL081HIDRCT-ND
U2: ESP32-DevKitC; Digikey Part Number 1965-ESP32-DEVKITC-VE-ND
U3: Opamp_Dual; SOIC-8_5.23x5.23mm_P1.27mm; Digikey Part Number 296-LM2904BIDRCT-ND
U4: MCP4821; SOIC-8_5.275x5.275mm_P1.27mm; Digikey Part Number MCP4821T-E/SNCT-ND

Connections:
/3V3: D1.1 (K), D3.1 (K), J5.1, U2.1 (3V3)
/CSn: J9.10, U2.29 (*GPIO5), U4.2 (~CS)
/EN: J5.2, U2.2 (CHIP_PU)
/GPIO0: J9.14, U2.25 (*GPIO0/BOOT/ADC2_CH1)
/GPIO2: J9.15, U2.24 (ADC2_CH2/*GPIO2)
/GPIO4: J9.13, U2.26 (ADC2_CH0/GPIO4)
/GPIO12: J5.13, U2.13 (*MTDI/GPIO12/ADC2_CH5)
/GPIO14: J5.12, U2.12 (MTMS/GPIO14/ADC2_CH6)
/GPIO16: J9.12, U2.27 (GPIO16)
/GPIO17: J9.11, U2.28 (GPIO17)
/GPIO21: J9.6, U2.33 (GPIO21)
/GPIO25: J5.9, U2.9 (DAC_1/ADC2_CH8/GPIO25)
/GPIO26: J5.10, U2.10 (DAC_2/ADC2_CH9/GPIO26)
/GPIO27: J5.11, U2.11 (ADC2_CH7/GPIO27)
/GPIO32: J5.7, U2.7 (32K_XP/GPIO32/ADC1_CH4)
/GPIO33: J5.8, U2.8 (32K_XN/GPIO33/ADC1_CH5)
/GPIO35: J5.6, U2.6 (VDET_2/GPIO35/ADC1_CH7)
/LDACn: J9.3, U2.36 (GPIO22), U4.5 (~LDAC)
/Lock: C6.2, D3.2 (A), D4.1 (K), J5.3, R4.1, U1.6, U2.3 (SENSOR_VP/GPIO36/ADC1_CH0)
/MISO: J9.8, U2.31 (GPIO19)
/MOSI: J9.2, U2.37 (GPIO23), U4.4 (SDI)
/PD: D1.2 (A), D2.1 (K), J3.1 (In), J5.4, U2.4 (SENSOR_VN/GPIO39/ADC1_CH3)
/PZT: J6.1 (In), RV1.1, U3.1
/SCLK: J9.9, U2.30 (GPIO18), U4.3 (SCK)
/TRIG: J5.5, R9.2, R10.1, U2.5 (VDET_1/GPIO34/ADC1_CH6)
/UART0 RX/GPIO3: J9.5, U2.34 (U0RXD/GPIO3)
/UART0 TX/GPIO1: J9.4, U2.35 (U0TXD/GPIO1)
/V_EXT: D5.2 (A), J1.1
/V_SYS: D5.1 (K), PS1.1 (+Vin), U2.19 (5V)
GND: C1.2, C2.1, C3.2, C4.2, C5.1, C9.1, C10.2, D2.2 (A), D4.2 (A), J1.2, J2.2 (Ext), J3.2 (Ext), J4.2 (Ext), J5.14, J5.15, J5.16, J6.2 (Ext), J9.1, J9.7, J9.16, PS1.2 (-Vin), PS1.5 (0V), R3.1, R10.2, R14.1, U2.14 (GND), U2.32 (GND), U2.38 (GND), U3.3 (+), U4.7 (Vss)
unnamed: C6.1, R2.1, R4.2, U1.2 (-)
unnamed: J2.1 (In), R2.2
unnamed: J4.1 (In), R9.1
unnamed: R1.2, R3.2, U1.3 (+)
unnamed: C7.1, R6.1, R7.2, U3.6 (-)
unnamed: R6.2, U4.8 (Vout)
unnamed: R12.2, R14.2, U3.5 (+)
unnamed: RV1.2, U3.2 (-)
unnamed: C7.2, R7.1, RV1.3, U3.7
VDD: C1.1, C3.1, C4.1, C10.1, PS1.6 (+Vout), R1.1, R12.1, U1.7 (V+), U3.8 (V+), U4.1 (Vdd), U4.6 (~SHDN)
VSS: C2.2, C5.2, C9.2, PS1.4 (-Vout), U1.4 (V-), U3.4 (V-)

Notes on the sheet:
Power VSYS is nominally +5 V PS generates +/- 5 V PS can handle 4.5 - 5.5 V. Needs a minimum current of 10 mA to meet output specifications, but lower loads will not cause damage
V_EXT should be +5 V
Output Signals DAC generates voltages from 0 V to VREF, where VREF is either 2.048 V or 4.096 V, which is software-selectable. 4.096 V is the default setting. Op-amps and resistors are use to generate bipolar output assuming VREF = 4.096 V and VDD = +5 V. Output of first op-amp is Vout = VDD*(1 + R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
Input signals
Lock = VDD*(1 + R4/R2)/(1 + R1/R3) - J2*R4/R2 = 1.5 V - J2 (VDD = 5 V)

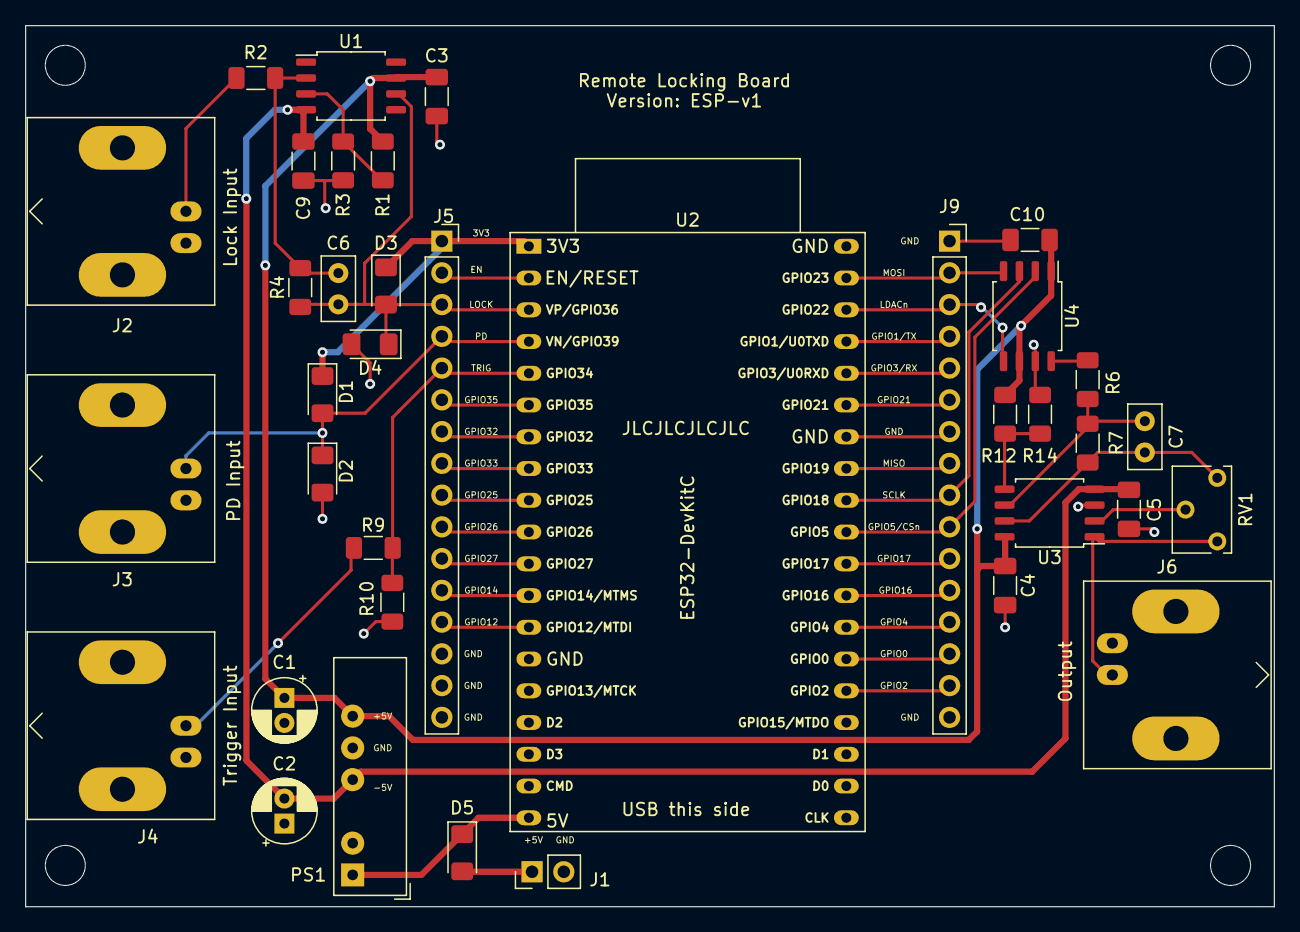
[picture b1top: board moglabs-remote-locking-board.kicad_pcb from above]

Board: 2 copper layers, 99.9 x 70.5 mm, 37 parts (0 on the bottom side), 41 nets.

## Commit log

2022-10-30 Dashboard, HOLD and PZT test
2022-10-30 PZT control, remove HOLD, bug fixes
2023-01-03 Initial commit, board designed with Raspberry Pi Pico W.
2023-01-04 Made FreeCAD model of housing w/o BNC holes
2023-01-15 Bug fixes + README update
2023-01-19 Minor changes to enclosure
2023-01-24 Updated path for footprints. Generated PDF of schematic
2023-01-25 Changed microcontroller to ESP12-DEVKIT-C. Updated FreeCAD design
2023-01-25 Updated input/output connectors to headers, modified board and FreeCAD
2023-01-26 Finialized design with pin headers for outputs. Added README
2023-01-26 Inputs/outputs now connected via BNC right-angle connectors.
    FreeCAD enclosure modified to account for new connectors. Board
    size is larger than previous version.
2023-01-30 Added voltage divider on trig input, changed output voltage range
    Also made board smaller for cheaper manufacturing.
2023-01-30 Removed current output, changed DAC to single channel
    Current input on the MOGLabs DLC doesn't allow for a DC bias in
    the absence of the fast lock. So I removed the current output,
    and therefore removed the 2 channel DAC. I have kept the 2 channel
    op-amp, and now I have two inverting amplifiers where the gain of the
    second stage can be adjusted through a trimpot.
2023-06-12 SPI tests + expand README
2023-06-12 Move enclosure to subdirectory
2023-06-15 Fix SPI DAC control
2023-06-15 Update parts list in README
2023-07-26 Secrets file for SSID/Password
2023-07-26 Update and rename secrets.h to example_secrets.h
    Needs to be done for .gitignore to work
2023-07-26 comment out example passwords and second esp type
2023-07-26 Hacked trigger to always fire mid data collection.
2023-07-28 Work in Progress. Reads data well now.
2023-07-29 UDP and matlab version
2023-07-31 Re added trigger
2023-07-31 Working but has noise. Need to filter output opamp
2023-07-31 update gitignore
2023-08-07 Added vertical position control to scope in matlab app.
2023-08-24 Updated matlab app to have stop/start
2023-09-14 Added ping and get ADC value commands + app
